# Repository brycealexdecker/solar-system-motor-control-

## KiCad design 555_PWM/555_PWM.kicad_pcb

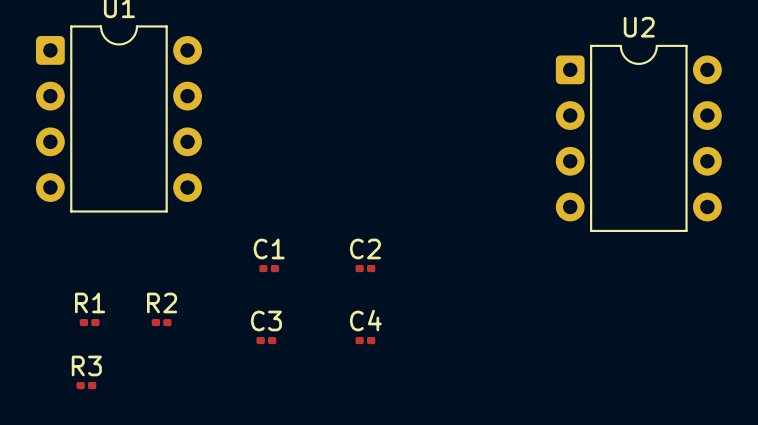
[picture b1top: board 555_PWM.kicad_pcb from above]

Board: 2 copper layers, 9 parts (0 on the bottom side), 7 nets, no tracks yet.

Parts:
C1: 1.5nF; C_0201_0603Metric
C2, C3: 10nF; C_0201_0603Metric
C4: 470pF; C_0201_0603Metric
R1: 5.6k; R_0201_0603Metric
R2: 2.2k; R_0201_0603Metric
R3: temp; R_0201_0603Metric
U1, U2: LM555xN; DIP-8_W7.62mm

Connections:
+5V: R1.1, R3.1, U1.8 (VCC), U2.8 (VCC)
GND: C1.2, C2.2, C3.2, C4.2, U1.1 (GND), U2.1 (GND)
unnamed: C2.1, U1.5 (CV)
unnamed: R1.2, R2.1, U1.7 (DIS)
unnamed: C1.1, R2.2, U1.2 (TR), U1.6 (THR)
unnamed: C3.1, U2.5 (CV)
unnamed: C4.1, R3.2, U2.2 (TR), U2.6 (THR), U2.7 (DIS)

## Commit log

2025-12-11 add commits to 3 way adjustable pot
2025-12-12 Design Phase Complete for Adjestable Pot
2025-12-23 New KiCad intteration 2
